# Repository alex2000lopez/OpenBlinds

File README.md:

# OpenBlinds
ESP12-based automatic blinds driver and controller

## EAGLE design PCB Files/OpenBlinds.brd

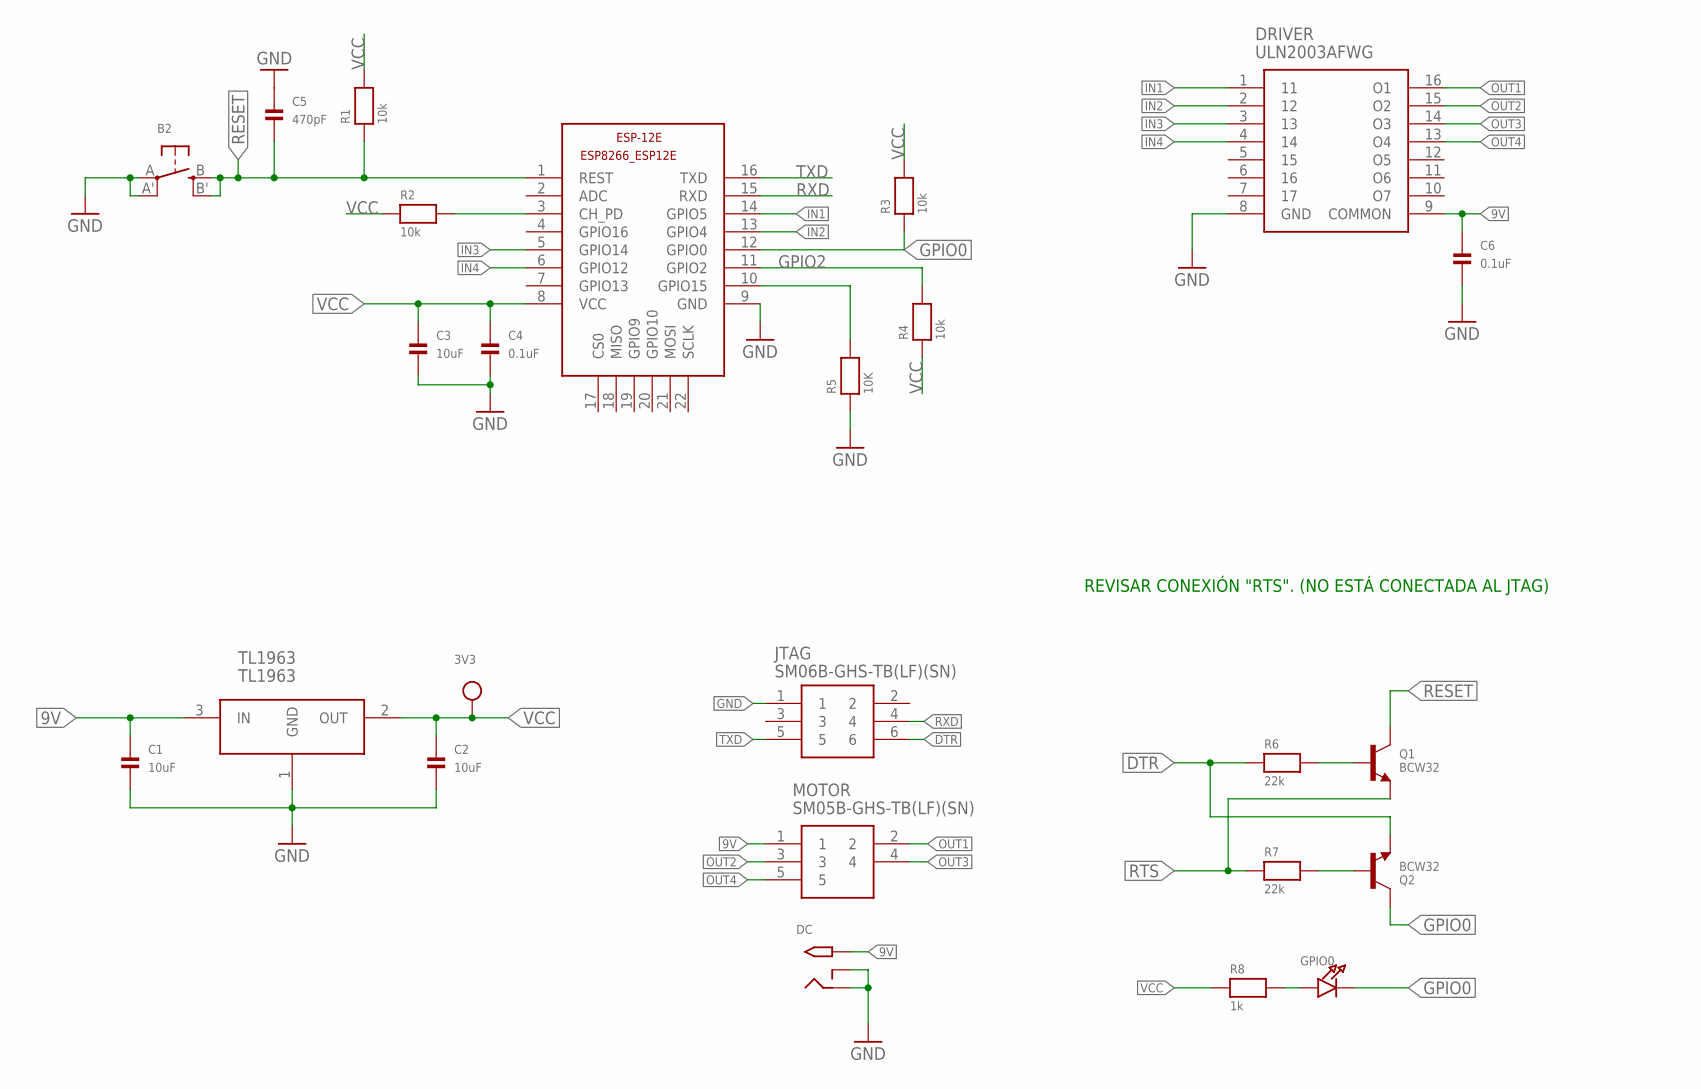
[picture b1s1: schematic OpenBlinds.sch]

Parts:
3V3: TESTPOINTROUND1MM; TESTPOINT_ROUND_1MM
B2: SWITCH_TACT_SMT4.6X2.8; BTN_KMR2_4.6X2.8
C1, C2, C3: 10uF; _0603
C4, C6: 0.1uF; _0603
C5: 470pF; _0603
DC: 2.1MMJACKTHM; PJ-102A
DRIVER: ULN2003AFWG; SOIC127P562X173-16N
ESP-12E: ESP-12E; ESP8266-ESP12E
GPIO0: LED0603; CHIPLED_0603
JTAG: SM06B-GHS-TB(LF)(SN); SM06B-GHS-TB
MOTOR: SM05B-GHS-TB(LF)(SN); SM05B-GHS-TB
Q1, Q2: BCW32; SOT23-R
R1, R2, R3, R4: 10k; _0603
R5: 10K; _0603
R6, R7: 22k; _0603
R8: 1k; _0603
TL1963: TL1963; SOT223

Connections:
9V: C1.1, C6.1, DC.TIP, DRIVER.9 (COMMON), MOTOR.1, TL1963.3 (IN)
DONE: ESP-12E.10 (GPIO15), R5.2
DTR: JTAG.6, Q2.2 (E), R6.1
GND: B2.A, B2.A' (P1), C1.2, C2.2, C3.2, C4.2, C5.1, C6.2, DC.RING, DC.RING_SW, DRIVER.8 (GND), ESP-12E.9 (GND), JTAG.1, R5.1, TL1963.1 (GND)
GPIO0: ESP-12E.12 (GPIO0), GPIO0.C, Q2.3 (C), R3.1
GPIO2: ESP-12E.11 (GPIO2), R4.2
IN1: DRIVER.1 (11), ESP-12E.14 (GPIO5)
IN2: DRIVER.2 (12), ESP-12E.13 (GPIO4)
IN3: DRIVER.3 (13), ESP-12E.5 (GPIO14)
IN4: DRIVER.4 (14), ESP-12E.6 (GPIO12)
unnamed: Q1.1 (B), R6.2
unnamed: Q2.1 (B), R7.2
unnamed: GPIO0.A, R8.2
unnamed: ESP-12E.3 (CH_PD), R2.2
OUT1: DRIVER.16 (O1), MOTOR.2
OUT2: DRIVER.15 (O2), MOTOR.3
OUT3: DRIVER.14 (O3), MOTOR.4
OUT4: DRIVER.13 (O4), MOTOR.5
RESET: B2.B (S), B2.B' (S1), C5.2, ESP-12E.1 (REST), Q1.3 (C), R1.1
RTS: Q1.2 (E), R7.1
RXD: ESP-12E.15 (RXD), JTAG.4
TXD: ESP-12E.16 (TXD), JTAG.5
VCC: 3V3.P$1, C2.1, C3.1, C4.1, ESP-12E.8 (VCC), R1.2, R2.1, R3.2, R4.1, R8.1, TL1963.2 (OUT)

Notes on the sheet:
REVISAR CONEXIÓN "RTS". (NO ESTÁ CONECTADA AL JTAG)

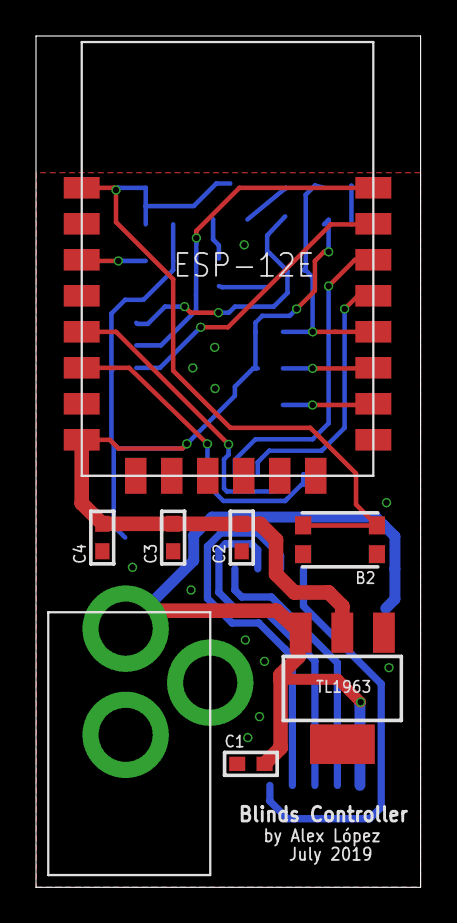
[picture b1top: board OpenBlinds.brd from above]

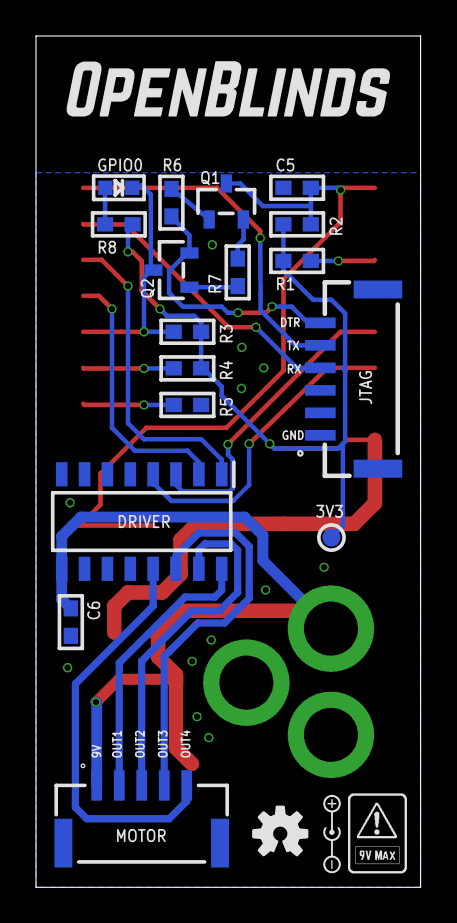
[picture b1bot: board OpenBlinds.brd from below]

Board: 2 copper layers, 21.4 x 47.3 mm, 26 parts (18 on the bottom side), 23 nets.

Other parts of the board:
U$1: OSHW-LOGO-S

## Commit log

2020-09-21 Files Uploaded

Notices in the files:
parts and their libraries:
microbuilder: This work is placed in the public domain, and may be freely used for commercial and non-commercial work with the following conditions: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
SparkFun-Aesthetics: Licensing: Creative Commons ShareAlike 4.0 International - https://creativecommons.org/licenses/by-sa/4.0
